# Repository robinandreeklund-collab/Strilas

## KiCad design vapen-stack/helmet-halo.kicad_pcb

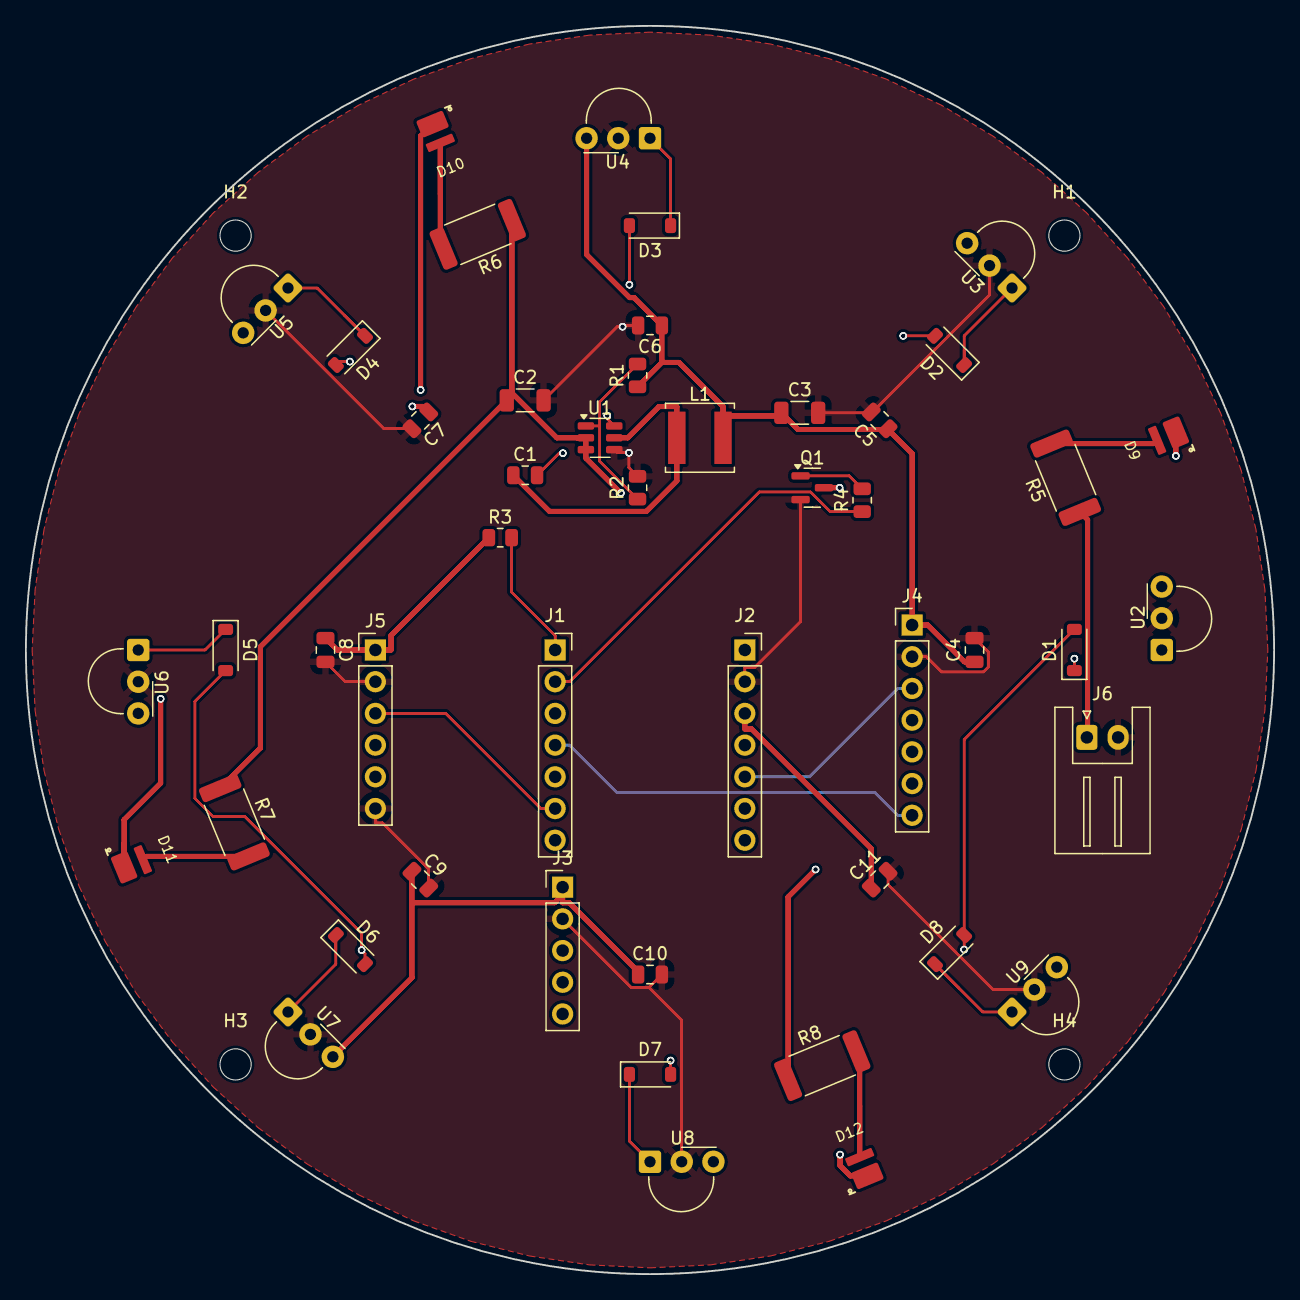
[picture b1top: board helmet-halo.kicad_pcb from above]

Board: 4 copper layers, 100.0 x 100.0 mm, 52 parts (0 on the bottom side), 29 nets.

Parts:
C1, C4, C5, C6, C7, C8, C9, C10, C11: C_0805_2012Metric
C2, C3: C_1206_3216Metric
D1, D2, D3, D4, D5, D6, D7, D8: D_SOD-123
D9, D10, D11, D12: IR_Emitter_OSRAM_OSLON_Black_SFH4725S
H1, H2, H3, H4: MountingHole_2.5mm
J1, J2: PinSocket_1x07_P2.54mm_Vertical
J3: PinHeader_1x05_P2.54mm_Vertical
J4: PinHeader_1x07_P2.54mm_Vertical
J5: PinHeader_1x06_P2.54mm_Vertical
J6: JST_XH_S2B-XH-A_1x02_P2.50mm_Horizontal
L1: L_Changjiang_FNR5040S
Q1: SOT-23
R1, R2, R3, R4: R_0805_2012Metric
R5, R6, R7, R8: R_2512_6332Metric
U1: TSOT-23-6
U2, U3, U4, U5, U6, U7, U8, U9: Vishay_MINIMOLD-3Pin

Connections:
+3V3: C3.1, C4.1, C5.1, C6.1, C7.1, C8.1, C9.1, C10.1, C11.1, J2.3, J3.1, J4.1, J5.1, L1.2, R1.1, R3.1, U2.3, U3.3, U4.3, U5.3, U6.3, U7.3, U8.3, U9.3
AMP_SD: J2.5, J4.3
BST: C1.2, U1.6
DATA: D1.2, D2.2, D3.2, D4.2, D5.2, D6.2, D7.2, D8.2, J1.1, R3.2
FB: R1.2, R2.1, U1.1
GND: C2.2, C3.2, C4.2, C5.2, C6.2, C7.2, C8.2, C9.2, C10.2, C11.2, J2.2, J3.2, J4.2, J5.2, J5.6, J6.2, Q1.2, R2.2, U1.4, U2.2, U3.2, U4.2, U5.2, U6.2, U7.2, U8.2, U9.2
GNSS_RX: J1.7, J3.4
GNSS_TX: J2.7, J3.3
I2S_BCLK: J1.3, J4.6, J5.5
I2S_DIN: J1.6, J5.3
I2S_DOUT: J1.5, J4.5
I2S_LRCK: J1.4, J4.7, J5.4
LED_A1: D9.1, R5.2
LED_A2: D10.1, R6.2
LED_A3: D11.1, R7.2
LED_A4: D12.1, R8.2
LED_CATH: D9.2, D10.2, D11.2, D12.2, Q1.3
LED_EN: J1.2, R4.1
unnamed: Q1.1, R4.2
OUT1: D1.1, U2.1
OUT2: D2.1, U3.1
OUT3: D3.1, U4.1
OUT4: D4.1, U5.1
OUT5: D5.1, U6.1
OUT6: D6.1, U7.1
OUT7: D7.1, U8.1
OUT8: D8.1, U9.1
SW: C1.1, L1.1, U1.5
VBAT: C2.1, J6.1, R5.1, R6.1, R7.1, R8.1, U1.2, U1.3

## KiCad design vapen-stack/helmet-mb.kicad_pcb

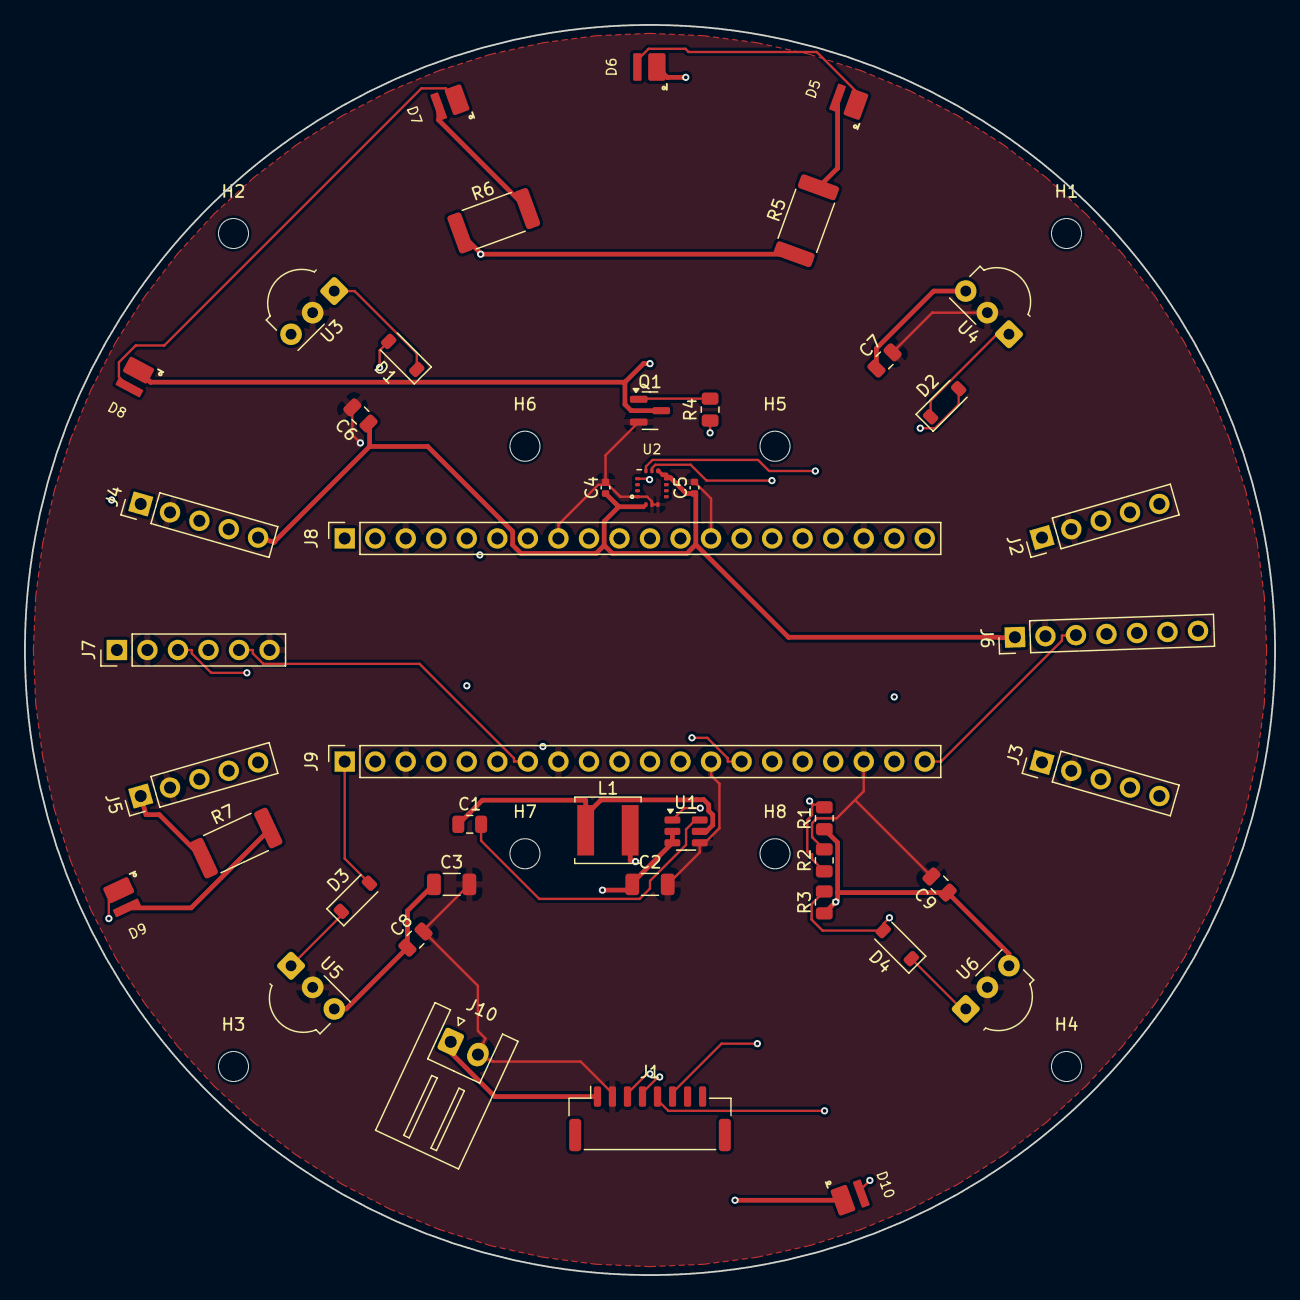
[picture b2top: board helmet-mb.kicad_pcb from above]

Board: 4 copper layers, 104.0 x 104.0 mm, 52 parts (0 on the bottom side), 34 nets.

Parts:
C1, C6, C7, C8, C9: C_0805_2012Metric
C2, C3: C_1206_3216Metric
C4, C5: C_0402_1005Metric
D1, D2, D3, D4: D_SOD-123
D5, D6, D7, D8, D9, D10: IR_Emitter_OSRAM_OSLON_Black_SFH4725S
H1, H2, H3, H4, H5, H6, H7, H8: MountingHole_2.5mm
J1: JST_GH_SM08B-GHS-TB_1x08-1MP_P1.25mm_Horizontal
J2, J3, J4, J5: PinHeader_1x05_P2.54mm_Vertical
J6: PinHeader_1x07_P2.54mm_Vertical
J7: PinHeader_1x06_P2.54mm_Vertical
J8, J9: PinSocket_1x20_P2.54mm_Vertical
J10: JST_XH_S2B-XH-A_1x02_P2.50mm_Horizontal
L1: L_Changjiang_FNR5040S
Q1: SOT-23
R1, R2, R3, R4: R_0805_2012Metric
R5, R6, R7: R_2512_6332Metric
U1: TSOT-23-6
U2: InvenSense_LGA-14_2.5x3mm_ICM-456xx
U3, U4, U5, U6: Vishay_MOLD-3Pin

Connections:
+3V3: C3.1, C4.1, C5.1, C6.1, C7.1, C8.1, C9.1, J2.5, J3.5, J4.5, J5.5, J6.1, J7.1, L1.2, R1.1, R3.1, U2.5, U2.8, U2.12, U3.3, U4.3, U5.3, U6.3
AMP_SD: J6.3, J9.20
BST: C1.2, U1.6
DATA_OB: D1.2, D2.2, D3.2, D4.2, J9.1, R3.2
DATA_P1: J2.3, J9.2
DATA_P2: J3.3, J9.4
DATA_P3: J4.3, J9.5
DATA_P4: J5.3, J9.6
FB: R1.2, R2.1, U1.1
GND: C2.2, C3.2, C4.2, C5.2, C6.2, C7.2, C8.2, C9.2, J1.2, J2.2, J3.2, J4.2, J5.2, J6.2, J7.2, J7.6, J8.3, J8.8, J8.13, J8.18, J9.3, J9.8, J9.13, J9.18, J10.2, Q1.2, R2.2, U1.4, U2.1, U2.6, U2.7, U3.2, U4.2, U5.2, U6.2
GNSS_RX: J1.4, J9.11
GNSS_TX: J1.3, J9.12
I2C_SCL: J1.6, J9.16, U2.13
I2C_SDA: J1.5, J9.17, U2.14
I2S_BCLK: J6.6, J7.5, J9.7
I2S_DIN: J7.3, J9.19
I2S_DOUT: J6.5, J9.10
I2S_LRCK: J6.7, J7.4, J9.9
IMU_INT: J9.14, U2.4
LED_A1: D5.1, R5.2
LED_A2: D7.1, R6.2
LED_A3: D9.1, R7.2
LED_CATH: D6.2, D8.2, D10.2, Q1.3
LED_EN: J2.4, J3.4, J4.4, J5.4, J9.15, R4.1
LED_M1: D5.2, D6.1
LED_M2: D7.2, D8.1
LED_M3: D9.2, D10.1
unnamed: Q1.1, R4.2
OB_OUT1: D1.1, U3.1
OB_OUT2: D2.1, U4.1
OB_OUT3: D3.1, U5.1
OB_OUT4: D4.1, U6.1
SW: C1.1, L1.1, U1.5
VBAT: C2.1, J1.1, J2.1, J3.1, J4.1, J5.1, J8.2, J10.1, R5.1, R6.1, R7.1, U1.2, U1.3

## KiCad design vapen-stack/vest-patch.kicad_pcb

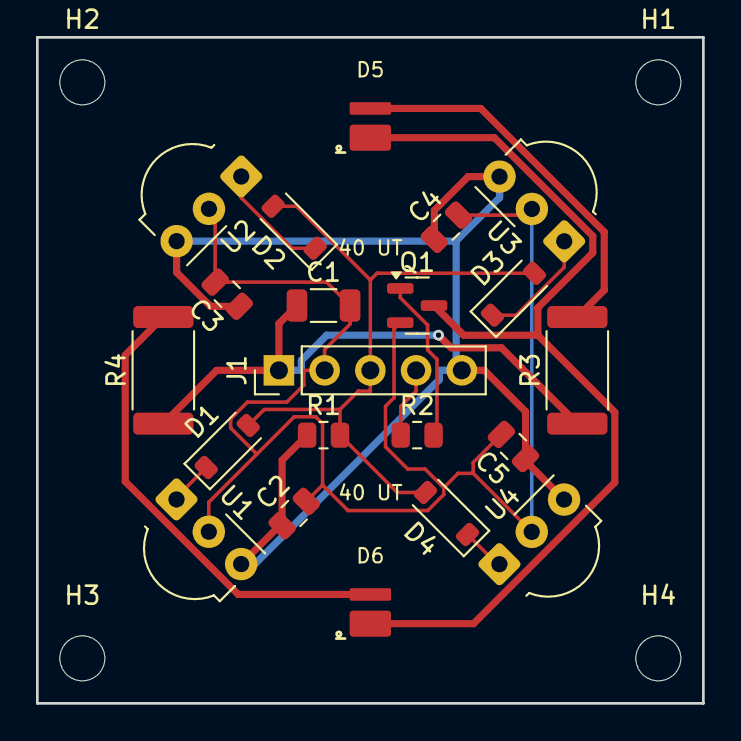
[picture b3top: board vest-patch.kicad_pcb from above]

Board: 2 copper layers, 37.0 x 37.0 mm, 25 parts (0 on the bottom side), 13 nets.

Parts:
C1: C_1206_3216Metric
C2, C3, C4, C5: C_0805_2012Metric
D1, D2, D3, D4: D_SOD-123
D5, D6: IR_Emitter_OSRAM_OSLON_Black_SFH4725S
H1, H2, H3, H4: MountingHole_2.5mm
J1: PinHeader_1x05_P2.54mm_Vertical
Q1: SOT-23
R1, R2: R_0805_2012Metric
R3, R4: R_2512_6332Metric
U1, U2, U3, U4: Vishay_MOLD-3Pin

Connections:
+3V3: C2.1, C3.1, C4.1, C5.1, J1.5, R1.1, U1.3, U2.3, U3.3, U4.3
DATA: D1.2, D2.2, D3.2, D4.2, J1.3, R1.2
GND: C1.2, C2.2, C3.2, C4.2, C5.2, J1.2, Q1.2, U1.2, U2.2, U3.2, U4.2
LED_A1: D5.1, R3.2
LED_A2: D6.1, R4.2
LED_CATH: D5.2, D6.2, Q1.3
LED_EN: J1.4, R2.1
unnamed: Q1.1, R2.2
OUT1: D1.1, U1.1
OUT2: D2.1, U2.1
OUT3: D3.1, U3.1
OUT4: D4.1, U4.1
VBAT: C1.1, J1.1, R3.1, R4.1

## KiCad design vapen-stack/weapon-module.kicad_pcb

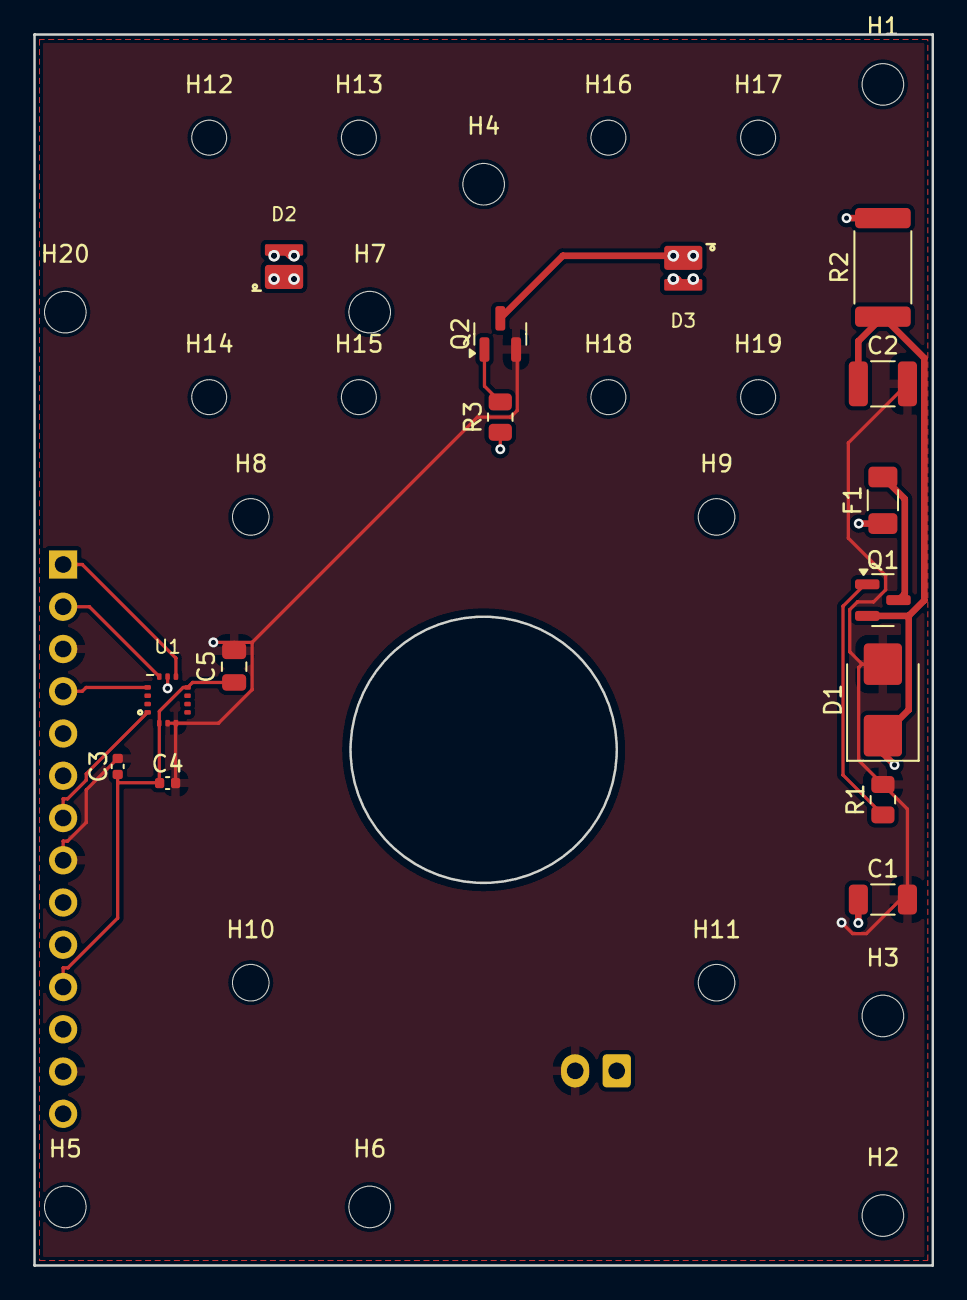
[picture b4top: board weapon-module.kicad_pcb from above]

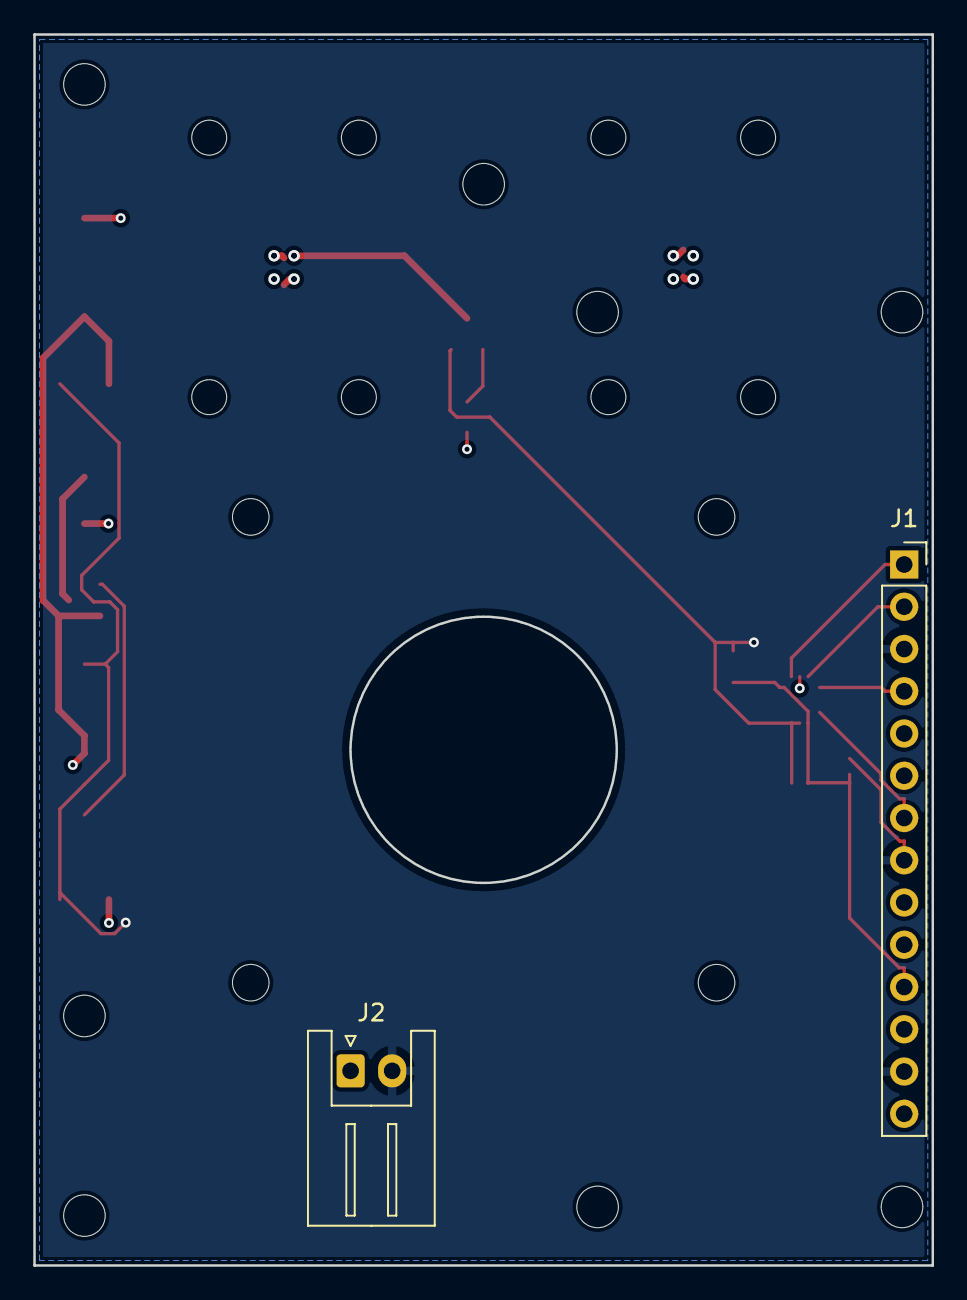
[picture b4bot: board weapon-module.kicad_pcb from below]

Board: 4 copper layers, 54.0 x 74.0 mm, 37 parts (2 on the bottom side), 16 nets.

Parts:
C1: C_1206_3216Metric
C2: C_1210_3225Metric
C3, C4: C_0402_1005Metric
C5: C_0805_2012Metric
D1: D_SMB
D2, D3: IR_Emitter_OSRAM_OSLON_Black_SFH4725S
F1: Fuse_1206_3216Metric
H1, H2, H3, H4, H5, H6, H7, H20: MountingHole_2.5mm
H8, H9, H10, H11: MountingHole_2.2mm_M2
H12, H13, H14, H15, H16, H17, H18, H19: MountingHole_2.1mm
J1: PinSocket_1x14_P2.54mm_Vertical
J2: JST_XH_S2B-XH-A_1x02_P2.50mm_Horizontal
Q1, Q2: SOT-23
R1, R3: R_0805_2012Metric
R2: R_2512_6332Metric
U1: InvenSense_LGA-14_2.5x3mm_ICM-456xx

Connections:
+3V3: C3.1, C4.1, C5.1, J1.11, U1.5, U1.8
GND: C1.2, C2.2, C3.2, C4.2, C5.2, D1.2, J1.3, J1.8, J1.13, J2.2, Q2.2, R1.2, U1.6, U1.7
IMU_INT: J1.4, U1.4
IR_MOD: J1.10, R3.1
LED_CATH: D3.2, Q2.3
LED_MID: D2.2, D3.1
MISO: J1.7, U1.1
MOSI: J1.2, U1.14
unnamed: Q1.1, R1.1
unnamed: D2.1, R2.2
Q1_GATE: Q2.1, R3.2
SCK: J1.6, U1.13
VBAT: C1.1, C2.1, D1.1, J1.14, Q1.2, R2.1
VBAT_F: F1.2, Q1.3
VBAT_IN: F1.1, J2.1
nCS: J1.1, U1.12
